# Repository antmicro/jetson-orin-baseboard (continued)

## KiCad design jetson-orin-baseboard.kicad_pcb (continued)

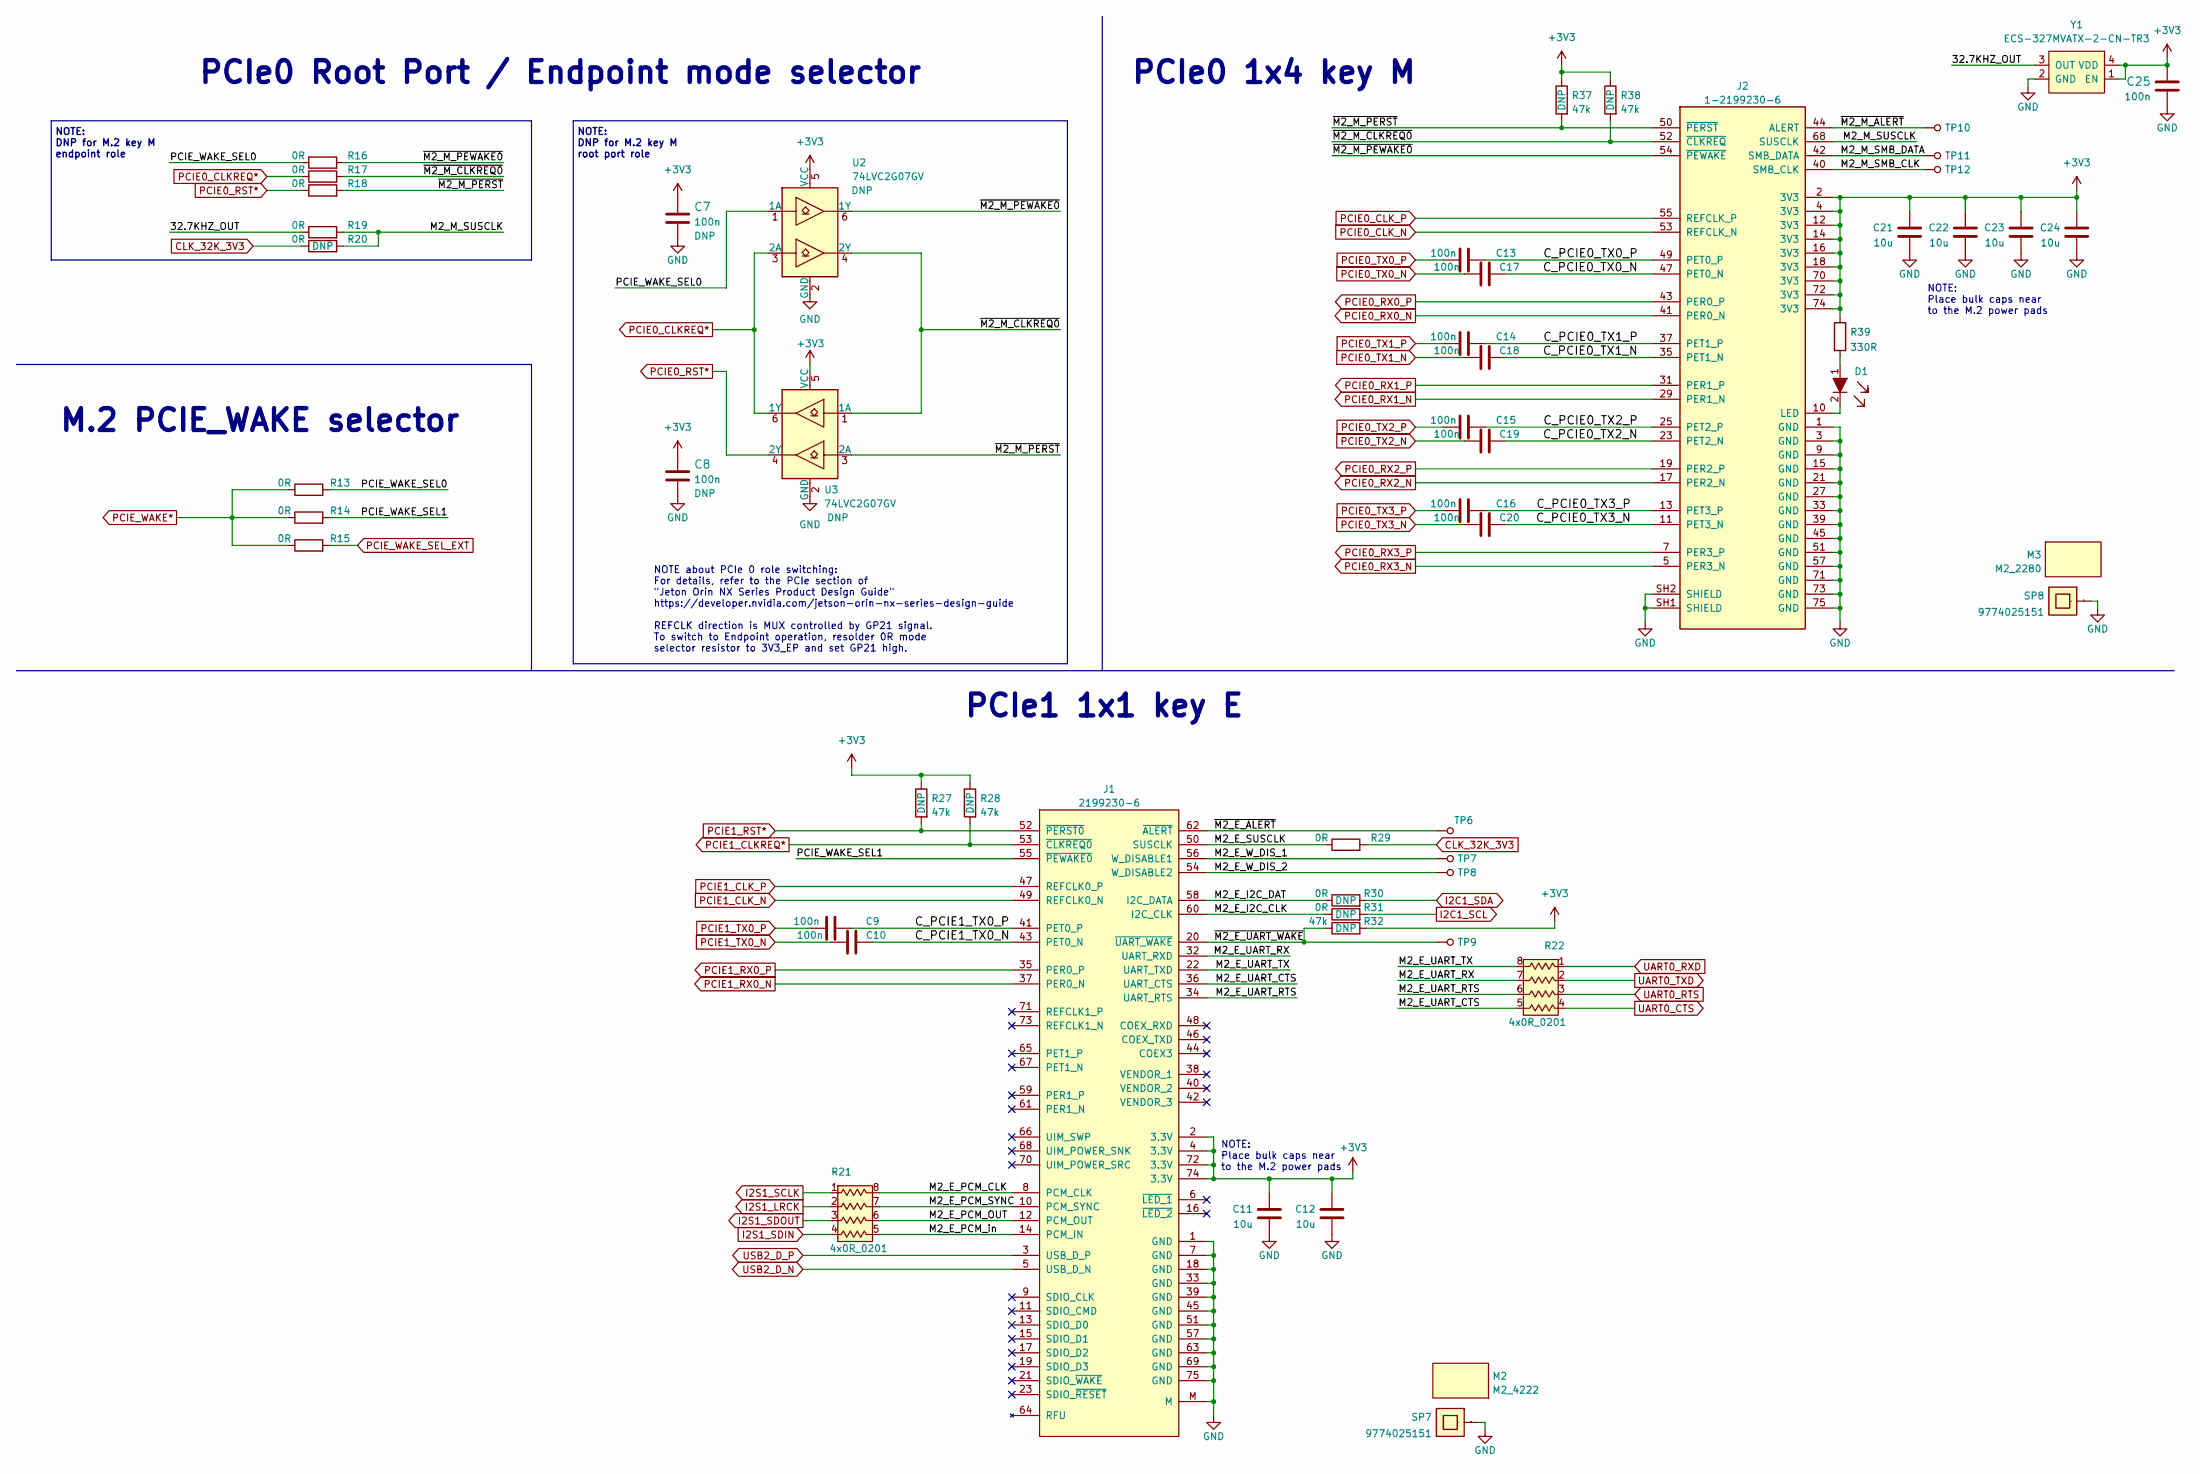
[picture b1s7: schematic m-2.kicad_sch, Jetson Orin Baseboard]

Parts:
C7, C8, C9, C10, C13, C14, C15, C16, C17, C18, C19, C20, C25: C_100n_0402; 0402-cap; MPN GRM155R61H104KE14D
C11, C12, C21, C22, C23, C24: C_10u_0603; 0603-cap; MPN GRM188R61A106KE69D
D1: LTST-C190GKT; LED_0603; MPN LTST-C190GKT
J1: 2199230-6; 2199230-4; MPN 2199230-6
J2: 1-2199230-6; MPN 1-2199230-6
M2: M2_4222; m2_4222
M3: M2_2280; m2_2280
R13, R14, R15, R16, R17, R18, R19, R20, R29, R30, R31: R_0R_0402; 0402-res; MPN ERJ2GE0R00X
R21, R22: 4x0R_0201_array; EXB18V; MPN EXB-18VR000X
R27, R28, R32, R37, R38: R_47k_0402; 0402-res; MPN MCMR04X4702FTL
R39: R_330R_0603; 0603-res; MPN CR0603-FX-3300GLF
SP7, SP8: 9774025151; MPN 9774025151
TP6, TP7, TP8, TP9, TP10, TP11, TP12: TP_SMD_0_75MM; Testpoint_smd_0_75mm
U2, U3: 74LVC2G07GV; SC-74; MPN 74LVC2G07GV,125
Y1: ECS-327MVATX-2-CN-TR3; Oscillator_SMD_ECS_2520MV-xxx-xx-4Pin_2.5x2.0mm; MPN ECS-327MVATX-2-CN-TR3

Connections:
+3V3: C7.1, C8.1, C11.1, C12.1, C21.1, C22.1, C23.1, C24.1, C25.1, J1.2 (3.3V), J1.4 (3.3V), J1.72 (3.3V), J1.74 (3.3V), J2.2 (3V3), J2.4 (3V3), J2.12 (3V3), J2.14 (3V3), J2.16 (3V3), J2.18 (3V3), J2.70 (3V3), J2.72 (3V3), J2.74 (3V3), R27.1, R28.1, R32.2, R37.1, R38.1, R39.2, U2.5 (VCC), U3.5 (VCC), Y1.1 (EN), Y1.4 (VDD); also elsewhere on the board
/M.2/32.7KHZ_OUT: R19.1, Y1.3 (OUT)
/M.2/C_PCIE0_TX0_N: C17.2, J2.47 (PET0_N)
/M.2/C_PCIE0_TX0_P: C13.2, J2.49 (PET0_P)
/M.2/C_PCIE0_TX1_N: C18.2, J2.35 (PET1_N)
/M.2/C_PCIE0_TX1_P: C14.2, J2.37 (PET1_P)
/M.2/C_PCIE0_TX2_N: C19.2, J2.23 (PET2_N)
/M.2/C_PCIE0_TX2_P: C15.2, J2.25 (PET2_P)
/M.2/C_PCIE0_TX3_N: C20.2, J2.11 (PET3_N)
/M.2/C_PCIE0_TX3_P: C16.2, J2.13 (PET3_P)
/M.2/C_PCIE1_TX0_N: C10.2, J1.43 (PET0_N)
/M.2/C_PCIE1_TX0_P: C9.2, J1.41 (PET0_P)
/M.2/M2_E_I2C_CLK: J1.60 (I2C_CLK), R31.1
/M.2/M2_E_I2C_DAT: J1.58 (I2C_DATA), R30.1
/M.2/M2_E_PCM_CLK: J1.8 (PCM_CLK), R21.8
/M.2/M2_E_PCM_OUT: J1.12 (PCM_OUT), R21.6
/M.2/M2_E_PCM_SYNC: J1.10 (PCM_SYNC), R21.7
/M.2/M2_E_PCM_in: J1.14 (PCM_IN), R21.5
/M.2/M2_E_SUSCLK: J1.50 (SUSCLK), R29.1
/M.2/M2_E_UART_CTS: J1.36 (UART_CTS), R22.5
/M.2/M2_E_UART_RTS: J1.34 (UART_RTS), R22.6
/M.2/M2_E_UART_RX: J1.32 (UART_RXD), R22.7
/M.2/M2_E_UART_TX: J1.22 (UART_TXD), R22.8
/M.2/M2_E_W_DIS_1: J1.56 (W_DISABLE1), TP7.1
/M.2/M2_E_W_DIS_2: J1.54 (W_DISABLE2), TP8.1
/M.2/M2_M_SMB_CLK: J2.40 (SMB_CLK), TP12.1
/M.2/M2_M_SMB_DATA: J2.42 (SMB_DATA), TP11.1
/M.2/M2_M_SUSCLK: J2.68 (SUSCLK), R19.2, R20.2
/M.2/PCIE_WAKE_SEL0: R13.2, R16.1, U2.1 (1A)
/M.2/PCIE_WAKE_SEL1: J1.55 (~PEWAKE0), R14.2
/M.2/~M2_E_ALERT: J1.62 (~ALERT), TP6.1
/M.2/~M2_E_UART_WAKE: J1.20 (~UART_WAKE), R32.1, TP9.1
/M.2/~M2_M_ALERT: J2.44 (ALERT), TP10.1
/M.2/~M2_M_CLKREQ0: J2.52 (~CLKREQ), R17.2, R38.2, U2.4 (2Y), U3.1 (1A)
/M.2/~M2_M_PERST: J2.50 (~PERST), R18.2, R37.2, U3.3 (2A)
/M.2/~M2_M_PEWAKE0: J2.54 (~PEWAKE), R16.2, U2.6 (1Y)
CLK_32K_3V3: R20.1, R29.2; also elsewhere on the board
GND: C7.2, C8.2, C11.2, C12.2, C21.2, C22.2, C23.2, C24.2, C25.2, J1.1 (GND), J1.7 (GND), J1.18 (GND), J1.33 (GND), J1.39 (GND), J1.45 (GND), J1.51 (GND), J1.57 (GND), J1.63 (GND), J1.69 (GND), J1.75 (GND), J1.M, J2.1 (GND), J2.3 (GND), J2.9 (GND), J2.15 (GND), J2.21 (GND), J2.27 (GND), J2.33 (GND), J2.39 (GND), J2.45 (GND), J2.51 (GND), J2.57 (GND), J2.71 (GND), J2.73 (GND), J2.75 (GND), J2.SH1 (SHIELD), J2.SH2 (SHIELD), SP7.1, SP8.1, U2.2 (GND), U3.2 (GND), Y1.2 (GND); also elsewhere on the board
I2C1_SCL: R31.2; also elsewhere on the board
I2C1_SDA: R30.2; also elsewhere on the board
I2S1_LRCK: R21.2; also elsewhere on the board
I2S1_SCLK: R21.1; also elsewhere on the board
I2S1_SDIN: R21.4; also elsewhere on the board
I2S1_SDOUT: R21.3; also elsewhere on the board
unnamed: D1.1, R39.1
unnamed: D1.2, J2.10 (LED)
PCIE0_CLKREQ*: R17.1, U2.3 (2A), U3.6 (1Y); also elsewhere on the board
PCIE0_CLK_N: J2.53 (REFCLK_N); also elsewhere on the board
PCIE0_CLK_P: J2.55 (REFCLK_P); also elsewhere on the board
PCIE0_RST*: R18.1, U3.4 (2Y); also elsewhere on the board
PCIE0_RX0_N: J2.41 (PER0_N); also elsewhere on the board
PCIE0_RX0_P: J2.43 (PER0_P); also elsewhere on the board
PCIE0_RX1_N: J2.29 (PER1_N); also elsewhere on the board
PCIE0_RX1_P: J2.31 (PER1_P); also elsewhere on the board
PCIE0_RX2_N: J2.17 (PER2_N); also elsewhere on the board
PCIE0_RX2_P: J2.19 (PER2_P); also elsewhere on the board
PCIE0_RX3_N: J2.5 (PER3_N); also elsewhere on the board
PCIE0_RX3_P: J2.7 (PER3_P); also elsewhere on the board
PCIE0_TX0_N: C17.1; also elsewhere on the board
PCIE0_TX0_P: C13.1; also elsewhere on the board
PCIE0_TX1_N: C18.1; also elsewhere on the board
PCIE0_TX1_P: C14.1; also elsewhere on the board
PCIE0_TX2_N: C19.1; also elsewhere on the board
PCIE0_TX2_P: C15.1; also elsewhere on the board
PCIE0_TX3_N: C20.1; also elsewhere on the board
PCIE0_TX3_P: C16.1; also elsewhere on the board
PCIE1_CLKREQ*: J1.53 (~CLKREQ0), R28.2; also elsewhere on the board
PCIE1_CLK_N: J1.49 (REFCLK0_N); also elsewhere on the board
PCIE1_CLK_P: J1.47 (REFCLK0_P); also elsewhere on the board
PCIE1_RST*: J1.52 (~PERST0), R27.2; also elsewhere on the board
PCIE1_RX0_N: J1.37 (PER0_N); also elsewhere on the board
PCIE1_RX0_P: J1.35 (PER0_P); also elsewhere on the board
PCIE1_TX0_N: C10.1; also elsewhere on the board
PCIE1_TX0_P: C9.1; also elsewhere on the board
PCIE_WAKE*: R13.1, R14.1, R15.1; also elsewhere on the board
PCIE_WAKE_SEL_EXT: R15.2; also elsewhere on the board
UART0_CTS: R22.4; also elsewhere on the board
UART0_RTS: R22.3; also elsewhere on the board
UART0_RXD: R22.1; also elsewhere on the board
UART0_TXD: R22.2; also elsewhere on the board
USB2_D_N: J1.5 (USB_D_N); also elsewhere on the board
USB2_D_P: J1.3 (USB_D_P); also elsewhere on the board

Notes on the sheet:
PCIe1 1x1 key E
NOTE about PCIe 0 role switching: For details, refer to the PCIe section of "Jeton Orin NX Series Product Design Guide" https://developer.nvidia.com/jetson-orin-nx-series-design-guide REFCLK direction is MUX controlled by GP21 signal. To switch to Endpoint operation, resolder 0R mode selector resis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
M.2 PCIE_WAKE selector
PCIe0 1x4 key M
NOTE: Place bulk caps near to the M.2 power pads
NOTE: DNP for M.2 key M root port role
PCIe0 Root Port / Endpoint mode selector
NOTE: DNP for M.2 key M endpoint role

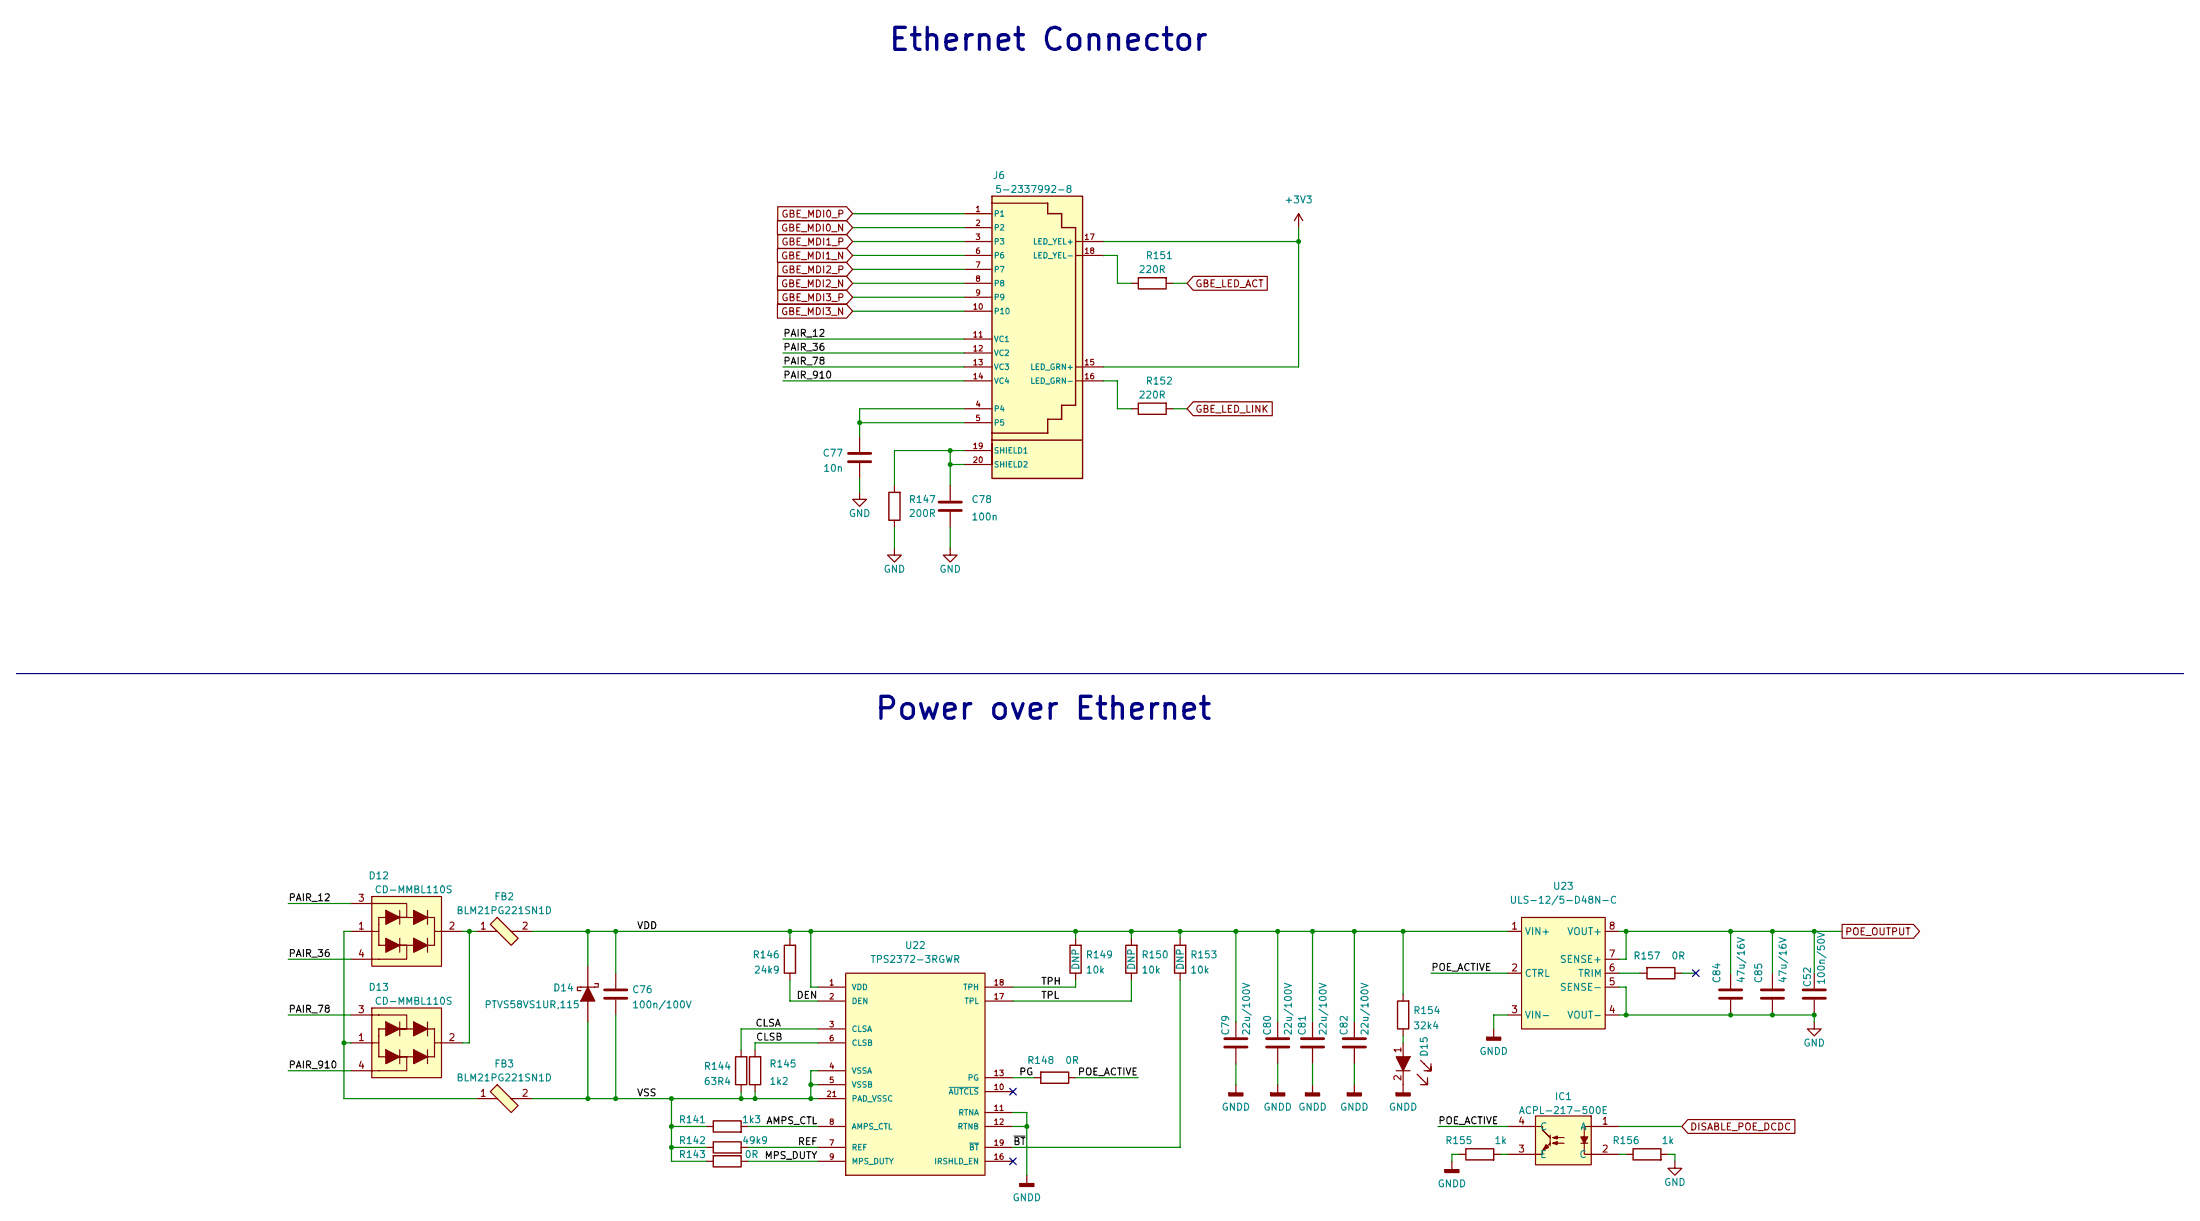
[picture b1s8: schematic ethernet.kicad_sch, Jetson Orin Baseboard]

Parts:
C52: C_100n_0402_50V; 0402-cap; MPN GRM155R71H104KE14D
C76: C_100n_0805_100V; 0805-cap; MPN CL21B104KCFNNNE
C77: C_10n_0402; 0402-cap; MPN 04025G103ZAT2A
C78: C_100n_0402; 0402-cap; MPN GRM155R61H104KE14D
C79, C80, C81, C82: C_22u_2220_100V; 2220-cap; MPN C5750X7S2A226M280KB
C84, C85: C_47u_16V_1206; 1206-cap; MPN C3216X5R1C476M160AB
D12, D13: CD-MMBL110S; DFN3538; MPN CD-MMBL110S
D14: PTVS58VS1UR,115; SOD-123F; MPN PTVS58VS1UR,115
D15: LTST-C190GKT; LED_0603; MPN LTST-C190GKT
FB2, FB3: BLM21PG221SN1D; 0805-res; MPN BLM21PG221SN1D
IC1: ACPL-217-500E; SOIC127P700X242-4N; MPN ACPL-217-500E; Mouser Part Number 630-ACPL-217-500E
J6: 5-2337992-8; MPN 5-2337992-8
R141: R_1k3_0603; 0603-res; MPN ERJ3GEYJ132V
R142: R_49k9_0402; 0402-res; MPN CRCW040249K9FKED
R143, R148, R157: R_0R_0603; 0603-res; MPN CR0603-J/-000ELF
R144: R_63R4_0603; 0603-res; MPN ERJPA3F63R4V
R145: R_1k2_0402; 0402-res; MPN ERJ2RKF1201X
R146: R_24k9_0402; 0402-res; MPN WR04X2492FTL
R147: R_200R_0402; 0402-res; MPN RC0402FR-07200RL
R149, R150, R153: R_10k_0402; 0402-res; MPN CRCW040210K0FKEDHP
R151, R152: R_220R_0402; 0402-res; MPN ERJ2GEJ221X
R154: R_32k4_0402; 0402-res; MPN ERA-2ARB3242X
R155, R156: R_1k_0603; 0603-res; MPN CR0603-JW-102ELF
U22: TPS2372-3RGWR; Texas_RGW0020B; MPN TPS2372-3RGWR
U23: ULS-12/5-D48N-C; ULS-12_5-D48N-C; MPN ULS-12/5-D48N-C

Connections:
+3V3: J6.15 (LED_GRN+), J6.17 (LED_YEL+); also elsewhere on the board
/Ethernet/AMPS_CTL: R141.2, U22.8 (AMPS_CTL)
/Ethernet/CLSA: R144.2, U22.3 (CLSA)
/Ethernet/CLSB: R145.2, U22.6 (CLSB)
/Ethernet/DEN: R146.1, U22.2 (DEN)
/Ethernet/MPS_DUTY: R143.1, U22.9 (MPS_DUTY)
/Ethernet/PAIR_12: D12.3, J6.11 (VC1)
/Ethernet/PAIR_36: D12.4, J6.12 (VC2)
/Ethernet/PAIR_78: D13.3, J6.13 (VC3)
/Ethernet/PAIR_910: D13.4, J6.14 (VC4)
/Ethernet/PG: R148.2, U22.13 (PG)
/Ethernet/POE_ACTIVE: IC1.4 (C), R148.1, U23.2 (CTRL)
/Ethernet/REF: R142.2, U22.7 (REF)
/Ethernet/TPH: R149.1, U22.18 (TPH)
/Ethernet/TPL: R150.1, U22.17 (TPL)
/Ethernet/VDD: C76.1, C79.1, C80.1, C81.1, C82.1, D14.K, FB2.2, R146.2, R149.2, R150.2, R153.2, R154.2, U22.1 (VDD), U23.1 (VIN+)
/Ethernet/VSS: C76.2, D14.A, FB3.2, R141.1, R142.1, R143.2, R144.1, R145.1, U22.4 (VSSA), U22.5 (VSSB), U22.21 (PAD_VSSC)
/Ethernet/~BT: R153.1, U22.19 (~BT)
DISABLE_POE_DCDC: IC1.1 (A); also elsewhere on the board
GBE_LED_ACT: R151.2; also elsewhere on the board
GBE_LED_LINK: R152.2; also elsewhere on the board
GBE_MDI0_N: J6.2; also elsewhere on the board
GBE_MDI0_P: J6.1; also elsewhere on the board
GBE_MDI1_N: J6.6; also elsewhere on the board
GBE_MDI1_P: J6.3; also elsewhere on the board
GBE_MDI2_N: J6.8; also elsewhere on the board
GBE_MDI2_P: J6.7; also elsewhere on the board
GBE_MDI3_N: J6.10; also elsewhere on the board
GBE_MDI3_P: J6.9; also elsewhere on the board
GND: C52.2, C77.2, C78.2, C84.2, C85.2, R147.1, R156.2, U23.4 (VOUT-), U23.5 (SENSE-); also elsewhere on the board
GNDD: C79.2, C80.2, C81.2, C82.2, D15.2, R155.1, U22.11 (RTNA), U22.12 (RTNB), U23.3 (VIN-)
unnamed: C77.1, J6.4, J6.5
unnamed: C78.1, J6.19 (SHIELD1), J6.20 (SHIELD2), R147.2
unnamed: D12.1, D13.1, FB3.1
unnamed: D12.2, D13.2, FB2.1
unnamed: D15.1, R154.1
unnamed: IC1.2 (C), R156.1
unnamed: IC1.3 (E), R155.2
unnamed: J6.16 (LED_GRN-), R152.1
unnamed: J6.18 (LED_YEL-), R151.1
unnamed: R157.2, U23.6 (TRIM)
POE_OUTPUT: C52.1, C84.1, C85.1, U23.7 (SENSE+), U23.8 (VOUT+); also elsewhere on the board

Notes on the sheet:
Power over Ethernet
Ethernet Connector

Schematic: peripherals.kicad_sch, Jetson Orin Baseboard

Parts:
C44, C48, C104, C108, C109, C110, C111, C112, C113: C_100n_0402; 0402-cap; MPN GRM155R61H104KE14D
C105, C106, C107, C114, C115: C_1u_0402; 0402-cap; MPN C1005X6S1A105K050BC
D26, D27: LTST-C190GKT; LED_0603; MPN LTST-C190GKT
D39, D40, D41, D42, D43, D44, D45, D46, D47, D48, D49, D50: TPD1E0B04DPYR; XDFN-2_1x0.60mm; MPN TPD1E0B04DPYR
J9: TC2050-IDC-NL; TC2050-IDC-NL_2x05_Vertical; MPN TC2050-IDC-NL
J10: 533980471; Molex_PicoBlade_53398-0471_1x04-1MP_P1.25mm_Vertical; MPN 0533980471
J11: ERF8-040-05.0-L-DV-K-TR; ERF8-040-XX.X-X-DV-XX; MPN ERF8-040-05.0-L-DV-K-TR
Q9, Q10: NX138BKMYL; DFN1006-3; MPN NX138BKMYL
R25: 4x0R_0201_array; EXB18V; MPN EXB-18VR000X
R26, R53, R54, R63, R64, R100, R101, R102: 4x330R_0402_array; R_Array_4x0402; MPN EXB-28V331JX
R55, R62, R120, R121, R215, R216, R217, R218: R_0R_0402; 0402-res; MPN ERJ2GE0R00X
R219: R_10k2_0402; 0402-res; MPN MCWR04X1022FTL
R222, R230: R_100k_0402; 0402-res; MPN CRCW0402100KFKEDHP
R223, R231: R_200R_0402; 0402-res; MPN RC0402FR-07200RL
R232, R242: R_10k_0402; 0402-res; MPN CRCW040210K0FKEDHP
R233, R234, R235, R247, R248: R_0R_0603; 0603-res; MPN CR0603-J/-000ELF
R335, R336: R_470R_0402; 0402-res; MPN CRCW0402470RFKED
S2, S3: B3U-3000PM; B3U-3000P; MPN B3U-3000PM
TP1, TP34, TP46, TP47: TP_SMD_0_75MM; Testpoint_smd_0_75mm
U29, U30: TPD4E05U06QDQARQ1; USON-10_2.5x1.0mm_P0.5mm; MPN TPD4E05U06QDQARQ1
U33: NTS0102GT; PSON50P100X195X50-8N; MPN NTS0102GT
U34: PCAL6408ABSHP; VQFN-16-1EP_3x3mm; MPN PCAL6408ABSHP

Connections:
3V3_STDB: R247.2; also elsewhere on the board
+1V8: C44.2, R219.2, R232.2, R234.2, R242.2, U33.3 (VCC_A), U33.6 (OE); also elsewhere on the board
+3V3: C104.1, R223.2, R231.2, R233.2, U34.14 (Vdd(p)), U34.15 (Vdd(I2C)); also elsewhere on the board
+5V: C48.2, J10.2, R235.1, U33.7 (VCC_B); also elsewhere on the board
+12V: R248.1
/Peripherals/1V8_CONN: C106.1, J11.73, R234.1
/Peripherals/3V3_CONN: C105.1, J11.67, J11.69, R233.1
/Peripherals/3V3_STDB_CONN: C114.1, J11.74, R247.1
/Peripherals/5V_CONN: C107.1, J11.77, J11.79, R235.2
/Peripherals/12V_CONN: C115.1, J11.78, J11.80, R248.2
/Peripherals/FAN_PWM_5V: J10.4, U33.8 (B1)
/Peripherals/FAN_TACH_5V: J10.3, U33.1 (B2)
/Peripherals/GPIO00_CONN: J11.44, R100.2
/Peripherals/GPIO01_CONN: J11.31, R26.2
/Peripherals/GPIO07_CONN: J11.33, R26.1
/Peripherals/GPIO09_CONN: J11.35, R53.4
/Peripherals/GPIO10_CONN: J11.39, R53.3
/Peripherals/GPIO11_CONN: J11.42, R100.3
/Peripherals/GPIO12_CONN: J11.40, R100.4
/Peripherals/GPIO13_CONN: J11.36, R64.1
/Peripherals/GPIOEX_ADDR: R218.2, U34.16 (ADDR)
/Peripherals/GPIOEX_I2C_SCL: R216.2, U34.12 (SCL)
/Peripherals/GPIOEX_I2C_SDA: R215.2, U34.13 (SDA)
/Peripherals/GPIOEX_P0_0: R25.8, U34.2 (P0)
/Peripherals/GPIOEX_P0_1: R25.7, U34.3 (P1)
/Peripherals/GPIOEX_P0_2: R25.6, U34.4 (P2)
/Peripherals/GPIOEX_P0_3: R25.5, U34.5 (P3)
/Peripherals/GPIOEX_RESET: R217.2, U34.1 (~RESET)
/Peripherals/I2S0_LRCK_CONN: J11.47, R54.3
/Peripherals/I2S0_SCLK_CONN: J11.46, R100.1
/Peripherals/I2S0_SDIN_CONN: J11.45, R54.4
/Peripherals/I2S0_SDOUT_CONN: J11.48, R101.4
/Peripherals/PCIE2_CLKREQ_CONN*: J11.29, R26.3
/Peripherals/PCIE2_RST_CONN*: J11.27, R26.4
/Peripherals/PCIE2_TX0_CONN_N: C108.2, D41.1, J11.9
/Peripherals/PCIE2_TX0_CONN_P: C109.2, D42.1, J11.11
/Peripherals/PCIE2_TX1_CONN_N: C112.2, D47.1, J11.3
/Peripherals/PCIE2_TX1_CONN_P: C110.2, D48.1, J11.5
/Peripherals/PCIE3_CLKREQ_CONN*: J11.32, R64.3
/Peripherals/PCIE_WAKE_SEL_EXT_CONN: J11.34, R64.2
/Peripherals/SPI1_MISO_CONN: J11.56, R101.1
/Peripherals/SPI1_MOSI_CONN: J11.54, R101.2
/Peripherals/SPI1_SCK_CONN: J11.52, R101.3
/Peripherals/SPIO_MISO_CONN: J11.55, R63.3
/Peripherals/SPIO_MOSI_CONN: J11.53, R54.1
/Peripherals/SPIO_SCK_CONN: J11.51, R54.2
/Peripherals/UART1_RXD_CONN: J11.43, R53.1
/Peripherals/UART1_TXD_CONN: J11.41, R53.2
/Peripherals/USBSS2_TX_CONN_N: C113.2, J11.21, U29.4 (IO3), U29.7 (IO3)
/Peripherals/USBSS2_TX_CONN_P: C111.2, J11.23, U29.5 (IO4), U29.6 (IO4)
/Peripherals/~SPI0_CS0_CONN: J11.57, R63.2
/Peripherals/~SPI0_CS1_CONN: J11.59, R63.1
/Peripherals/~SPI1_CS0_CONN: J11.58, R102.2
/Peripherals/~SPI1_CS1_CONN: J11.60, R102.1
CAN_RX: R335.1; also elsewhere on the board
CAN_TX: R336.1; also elsewhere on the board
CSIA_PEN: R25.1; also elsewhere on the board
CSIB_PEN: R25.2; also elsewhere on the board
DEBUG_RXD: J9.2; also elsewhere on the board
DEBUG_TXD: J9.1; also elsewhere on the board
DISABLE_POE_DCDC: R25.4; also elsewhere on the board
EEPROM_PWR: J9.10; also elsewhere on the board
FAN_PWM: U33.5 (A1); also elsewhere on the board
FAN_TACH: U33.4 (A2); also elsewhere on the board
GND: C44.1, C48.1, C104.2, C105.2, C106.2, C107.2, C114.2, C115.2, D39.2, D40.2, D41.2, D42.2, D43.2, D44.2, D45.2, D46.2, D47.2, D48.2, D49.2, D50.2, J9.5, J10.1, J11.1, J11.2, J11.4, J11.7, J11.10, J11.13, J11.16, J11.19, J11.22, J11.25, J11.28, J11.37, J11.38, J11.49, J11.50, J11.61, J11.62, J11.71, J11.72, J11.75, J11.76, Q9.2 (S), Q10.2 (S), R217.1, R218.1, R222.1, R230.1, S2.2, S3.2, U29.3 (GND), U29.8 (GND), U30.3 (GND), U30.8 (GND), U33.2 (GND), U34.6 (Vss); also elsewhere on the board
GPIO00: R100.6; also elsewhere on the board
GPIO01: R26.6; also elsewhere on the board
GPIO07: R26.5; also elsewhere on the board
GPIO09: R53.8; also elsewhere on the board
GPIO10: R53.7; also elsewhere on the board
GPIO11: R100.7; also elsewhere on the board
GPIO12: R100.8; also elsewhere on the board
GPIO13: R64.5; also elsewhere on the board
I2C2_SCL: R121.2, U30.5 (IO4), U30.6 (IO4); also elsewhere on the board
I2C2_SDA: R120.2, U30.4 (IO3), U30.7 (IO3); also elsewhere on the board
I2S0_LRCK: R54.7; also elsewhere on the board
I2S0_SCLK: R100.5; also elsewhere on the board
I2S0_SDIN: R54.8; also elsewhere on the board
I2S0_SDOUT: R101.8; also elsewhere on the board
unnamed: D26.1, R223.1
unnamed: D26.2, Q9.3 (D)
unnamed: D27.1, R231.1
unnamed: D27.2, Q10.3 (D)
unnamed: J11.63, R55.2
unnamed: J11.64, R120.1
unnamed: J11.65, R62.2
unnamed: J11.66, R121.1
unnamed: J11.68, R335.2
unnamed: J11.70, R336.2
unnamed: TP1.1, U34.7 (P4)
unnamed: TP34.1, U34.8 (P5)
unnamed: TP46.1, U34.9 (P6)
unnamed: TP47.1, U34.10 (P7)
PCIE2_CLKREQ*: R26.7; also elsewhere on the board
PCIE2_CLK_N: D43.1, J11.15; also elsewhere on the board
PCIE2_CLK_P: D44.1, J11.17; also elsewhere on the board
PCIE2_RST*: R26.8; also elsewhere on the board
PCIE2_RX0_N: D39.1, J11.12; also elsewhere on the board
PCIE2_RX0_P: D40.1, J11.14; also elsewhere on the board
PCIE2_RX1_N: D45.1, J11.6; also elsewhere on the board
PCIE2_RX1_P: D46.1, J11.8; also elsewhere on the board
PCIE2_TX0_N: C108.1; also elsewhere on the board
PCIE2_TX0_P: C109.1; also elsewhere on the board
PCIE2_TX1_N: C112.1; also elsewhere on the board
PCIE2_TX1_P: C110.1; also elsewhere on the board
PCIE3_CLKREQ*: R64.7; also elsewhere on the board
PCIE3_CLK_N: D49.1, J11.18; also elsewhere on the board
PCIE3_CLK_P: D50.1, J11.20; also elsewhere on the board
PCIE3_RST_CONN*: J11.30, R64.4, R64.8
PCIE_WAKE_SEL_EXT: R64.6; also elsewhere on the board
PDC_MISO: J9.8; also elsewhere on the board
PDC_MOSI: J9.9; also elsewhere on the board
PDC_SCLK: J9.7; also elsewhere on the board
SPI1_MISO: R101.5; also elsewhere on the board
SPI1_MOSI: R101.6; also elsewhere on the board
SPI1_SCK: R101.7; also elsewhere on the board
SPIO_MISO: R63.8; also elsewhere on the board
SPIO_MOSI: R54.5; also elsewhere on the board
SPIO_SCK: R54.6; also elsewhere on the board
SYS_SCL: J9.4, R62.1, R216.1, U30.2 (IO2), U30.9 (IO2); also elsewhere on the board
SYS_SDA: J9.3, R55.1, R215.1, U30.1 (IO1), U30.10 (IO1); also elsewhere on the board
UART1_RXD: R53.5; also elsewhere on the board
UART1_TXD: R53.6; also elsewhere on the board
USBC1_PEN: R25.3; also elsewhere on the board
USBSS1_RX_N: J11.24, U29.1 (IO1), U29.10 (IO1); also elsewhere on the board
USBSS1_RX_P: J11.26, U29.2 (IO2), U29.9 (IO2); also elsewhere on the board
USBSS1_TX_N: C113.1; also elsewhere on the board
USBSS1_TX_P: C111.1; also elsewhere on the board
USER_BTN0: R232.1, S2.1; also elsewhere on the board
USER_BTN1: R242.1, S3.1; also elsewhere on the board
USER_LED0: Q9.1 (G), R222.2; also elsewhere on the board
USER_LED1: Q10.1 (G), R230.2; also elsewhere on the board
~GPIO_INT: R219.1, U34.11 (~INT); also elsewhere on the board
~PDC_CS: J9.6; also elsewhere on the board
~SPI0_CS0: R63.7; also elsewhere on the board
~SPI0_CS1: R63.6; also elsewhere on the board
~SPI1_CS0: R102.8; also elsewhere on the board
~SPI1_CS1: R102.7; also elsewhere on the board

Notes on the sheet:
TAG-CONNECT
Fan connector
Expansion connector
LED indicators
Expansion connector resistors
GPIO expander
Debug connector
LOW POWER ONLY FOR LEVEL SHIFTERS
Buttons
